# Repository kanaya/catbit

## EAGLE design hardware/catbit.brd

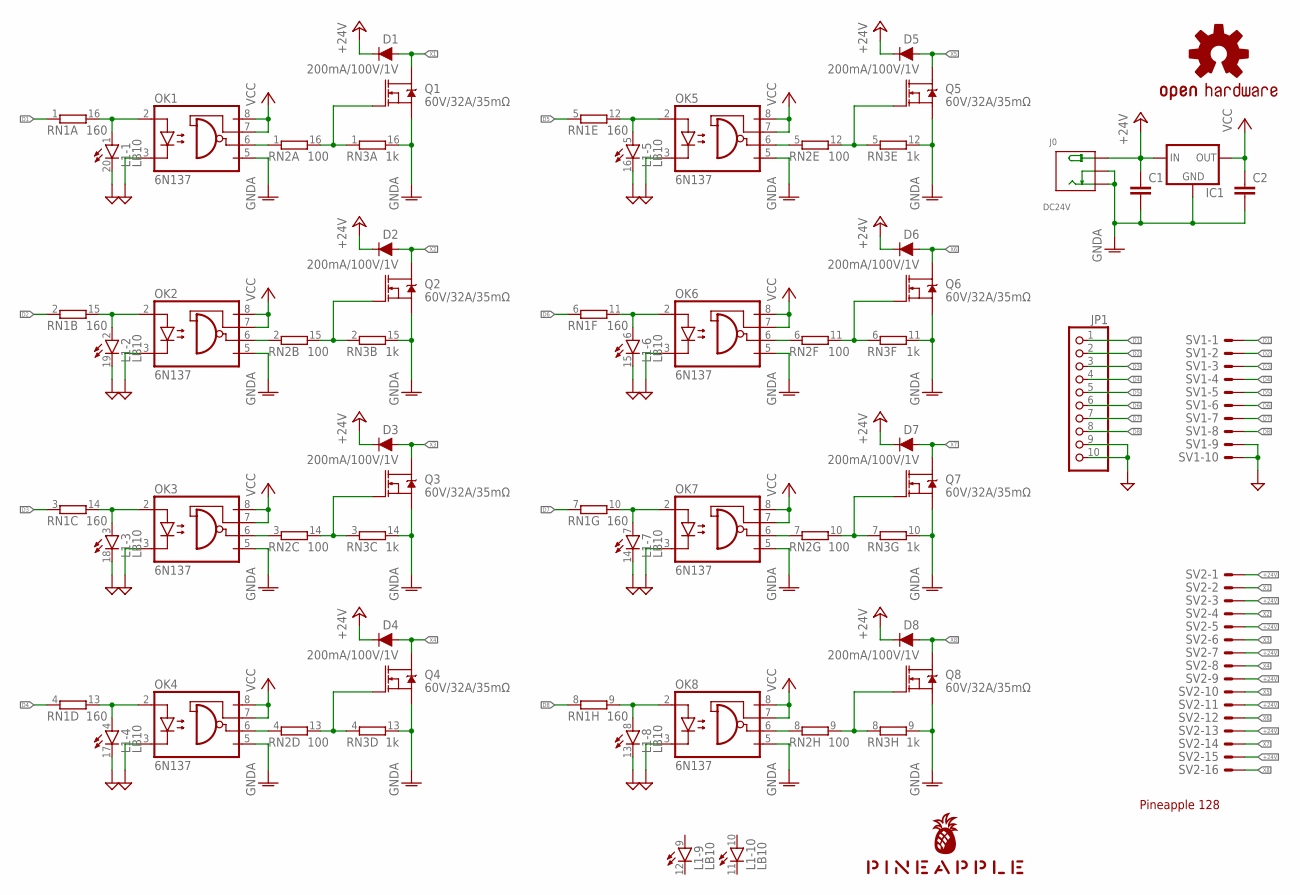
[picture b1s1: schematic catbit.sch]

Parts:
C1, C2: C-EU025-024X044; C025-024X044
D1, D2, D3, D4, D5, D6, D7, D8: 200mA/100V/1V; DIODE-1N4148
IC1: 78XXS
J0: DC24V; 3P-L14.2*W11.0*H9.0MM
JP1: PINHD-1X10; 1X10
L1: LB10
LOGO1: OSHW-LOGOS-COPPER; OSHW-LOGO-S_COPPER
OK1, OK2, OK3, OK4, OK5, OK6, OK7, OK8: 6N137; DIL08
Q1, Q2, Q3, Q4, Q5, Q6, Q7, Q8: 60V/32A/35mΩ; TO220V
RN1: 160; DIL16
RN2: 100; DIL16
RN3: 1k; DIL16
SV1: ML10LE; ML10L
SV2: ML16LE; ML16L
U$1: PINEAPPLE450_SILK

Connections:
+24V: C1.1, D1.C, D2.C, D3.C, D4.C, D5.C, D6.C, D7.C, D8.C, IC1.IN, J0.+, SV2.1, SV2.3, SV2.5, SV2.7, SV2.9, SV2.11, SV2.13, SV2.15
D1: JP1.1, RN1.1, SV1.1
D2: JP1.2, RN1.2 (1), SV1.2
D3: JP1.3, RN1.3 (1), SV1.3
D4: JP1.4, RN1.4 (1), SV1.4
D5: JP1.5, RN1.5 (1), SV1.5
D6: JP1.6, RN1.6 (1), SV1.6
D7: JP1.7, RN1.7 (1), SV1.7
D8: JP1.8, RN1.8 (1), SV1.8
GND: JP1.9, JP1.10, L1.13 (C), L1.14 (C), L1.15 (C), L1.16 (C), L1.17 (C), L1.18 (C), L1.19 (C), L1.20 (C), OK1.3 (C), OK2.3 (C), OK3.3 (C), OK4.3 (C), OK5.3 (C), OK6.3 (C), OK7.3 (C), OK8.3 (C), SV1.9, SV1.10
GNDA: C1.2, C2.2, IC1.GND, J0.-1 (-), J0.-2 (CDN), OK1.5 (GND), OK2.5 (GND), OK3.5 (GND), OK4.5 (GND), OK5.5 (GND), OK6.5 (GND), OK7.5 (GND), OK8.5 (GND), Q1.3 (S), Q2.3 (S), Q3.3 (S), Q4.3 (S), Q5.3 (S), Q6.3 (S), Q7.3 (S), Q8.3 (S), RN3.9 (2), RN3.10 (2), RN3.11 (2), RN3.12 (2), RN3.13 (2), RN3.14 (2), RN3.15 (2), RN3.16 (2)
unnamed: L1.1 (A), OK1.2 (A), RN1.16 (2)
unnamed: OK1.6 (VO), RN2.1
unnamed: Q1.1 (G), RN2.16 (2), RN3.1
unnamed: L1.2 (A), OK2.2 (A), RN1.15 (2)
unnamed: OK2.6 (VO), RN2.2 (1)
unnamed: Q2.1 (G), RN2.15 (2), RN3.2 (1)
unnamed: L1.3 (A), OK3.2 (A), RN1.14 (2)
unnamed: OK3.6 (VO), RN2.3 (1)
unnamed: Q3.1 (G), RN2.14 (2), RN3.3 (1)
unnamed: L1.4 (A), OK4.2 (A), RN1.13 (2)
unnamed: OK4.6 (VO), RN2.4 (1)
unnamed: Q4.1 (G), RN2.13 (2), RN3.4 (1)
unnamed: L1.5 (A), OK5.2 (A), RN1.12 (2)
unnamed: OK5.6 (VO), RN2.5 (1)
unnamed: Q5.1 (G), RN2.12 (2), RN3.5 (1)
unnamed: L1.6 (A), OK6.2 (A), RN1.11 (2)
unnamed: OK6.6 (VO), RN2.6 (1)
unnamed: Q6.1 (G), RN2.11 (2), RN3.6 (1)
unnamed: L1.7 (A), OK7.2 (A), RN1.10 (2)
unnamed: OK7.6 (VO), RN2.7 (1)
unnamed: Q7.1 (G), RN2.10 (2), RN3.7 (1)
unnamed: L1.8 (A), OK8.2 (A), RN1.9 (2)
unnamed: OK8.6 (VO), RN2.8 (1)
unnamed: Q8.1 (G), RN2.9 (2), RN3.8 (1)
VCC: C2.1, IC1.OUT, OK1.7 (VE), OK1.8 (VCC), OK2.7 (VE), OK2.8 (VCC), OK3.7 (VE), OK3.8 (VCC), OK4.7 (VE), OK4.8 (VCC), OK5.7 (VE), OK5.8 (VCC), OK6.7 (VE), OK6.8 (VCC), OK7.7 (VE), OK7.8 (VCC), OK8.7 (VE), OK8.8 (VCC)
X1: D1.A, Q1.2 (D), SV2.2
X2: D2.A, Q2.2 (D), SV2.4
X3: D3.A, Q3.2 (D), SV2.6
X4: D4.A, Q4.2 (D), SV2.8
X5: D5.A, Q5.2 (D), SV2.10
X6: D6.A, Q6.2 (D), SV2.12
X7: D7.A, Q7.2 (D), SV2.14
X8: D8.A, Q8.2 (D), SV2.16

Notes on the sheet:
Pineapple 128

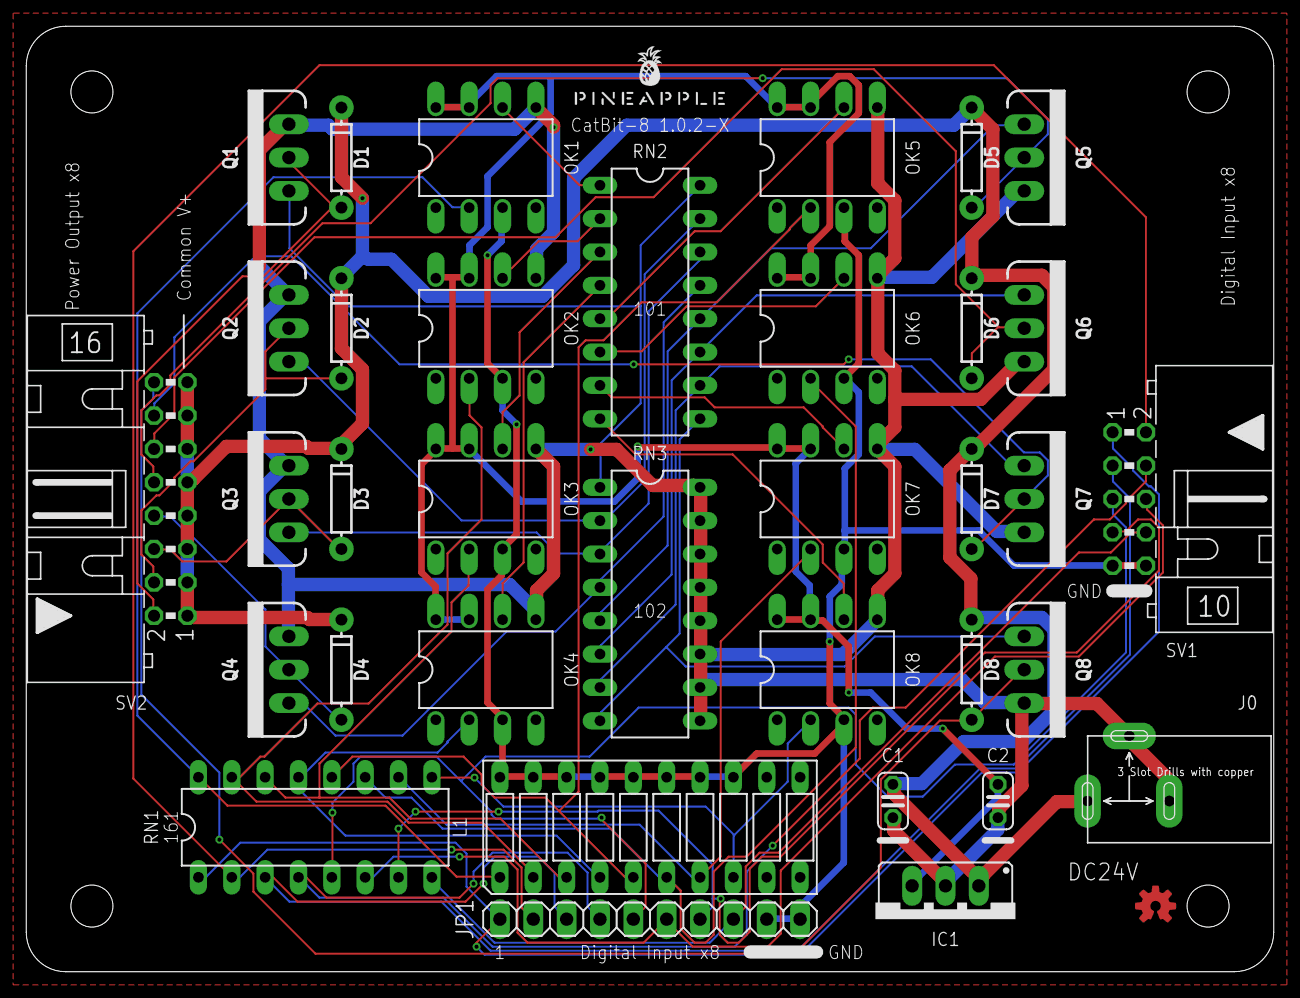
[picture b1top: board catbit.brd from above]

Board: 2 copper layers, 94.9 x 71.9 mm, 37 parts (0 on the bottom side), 44 nets.

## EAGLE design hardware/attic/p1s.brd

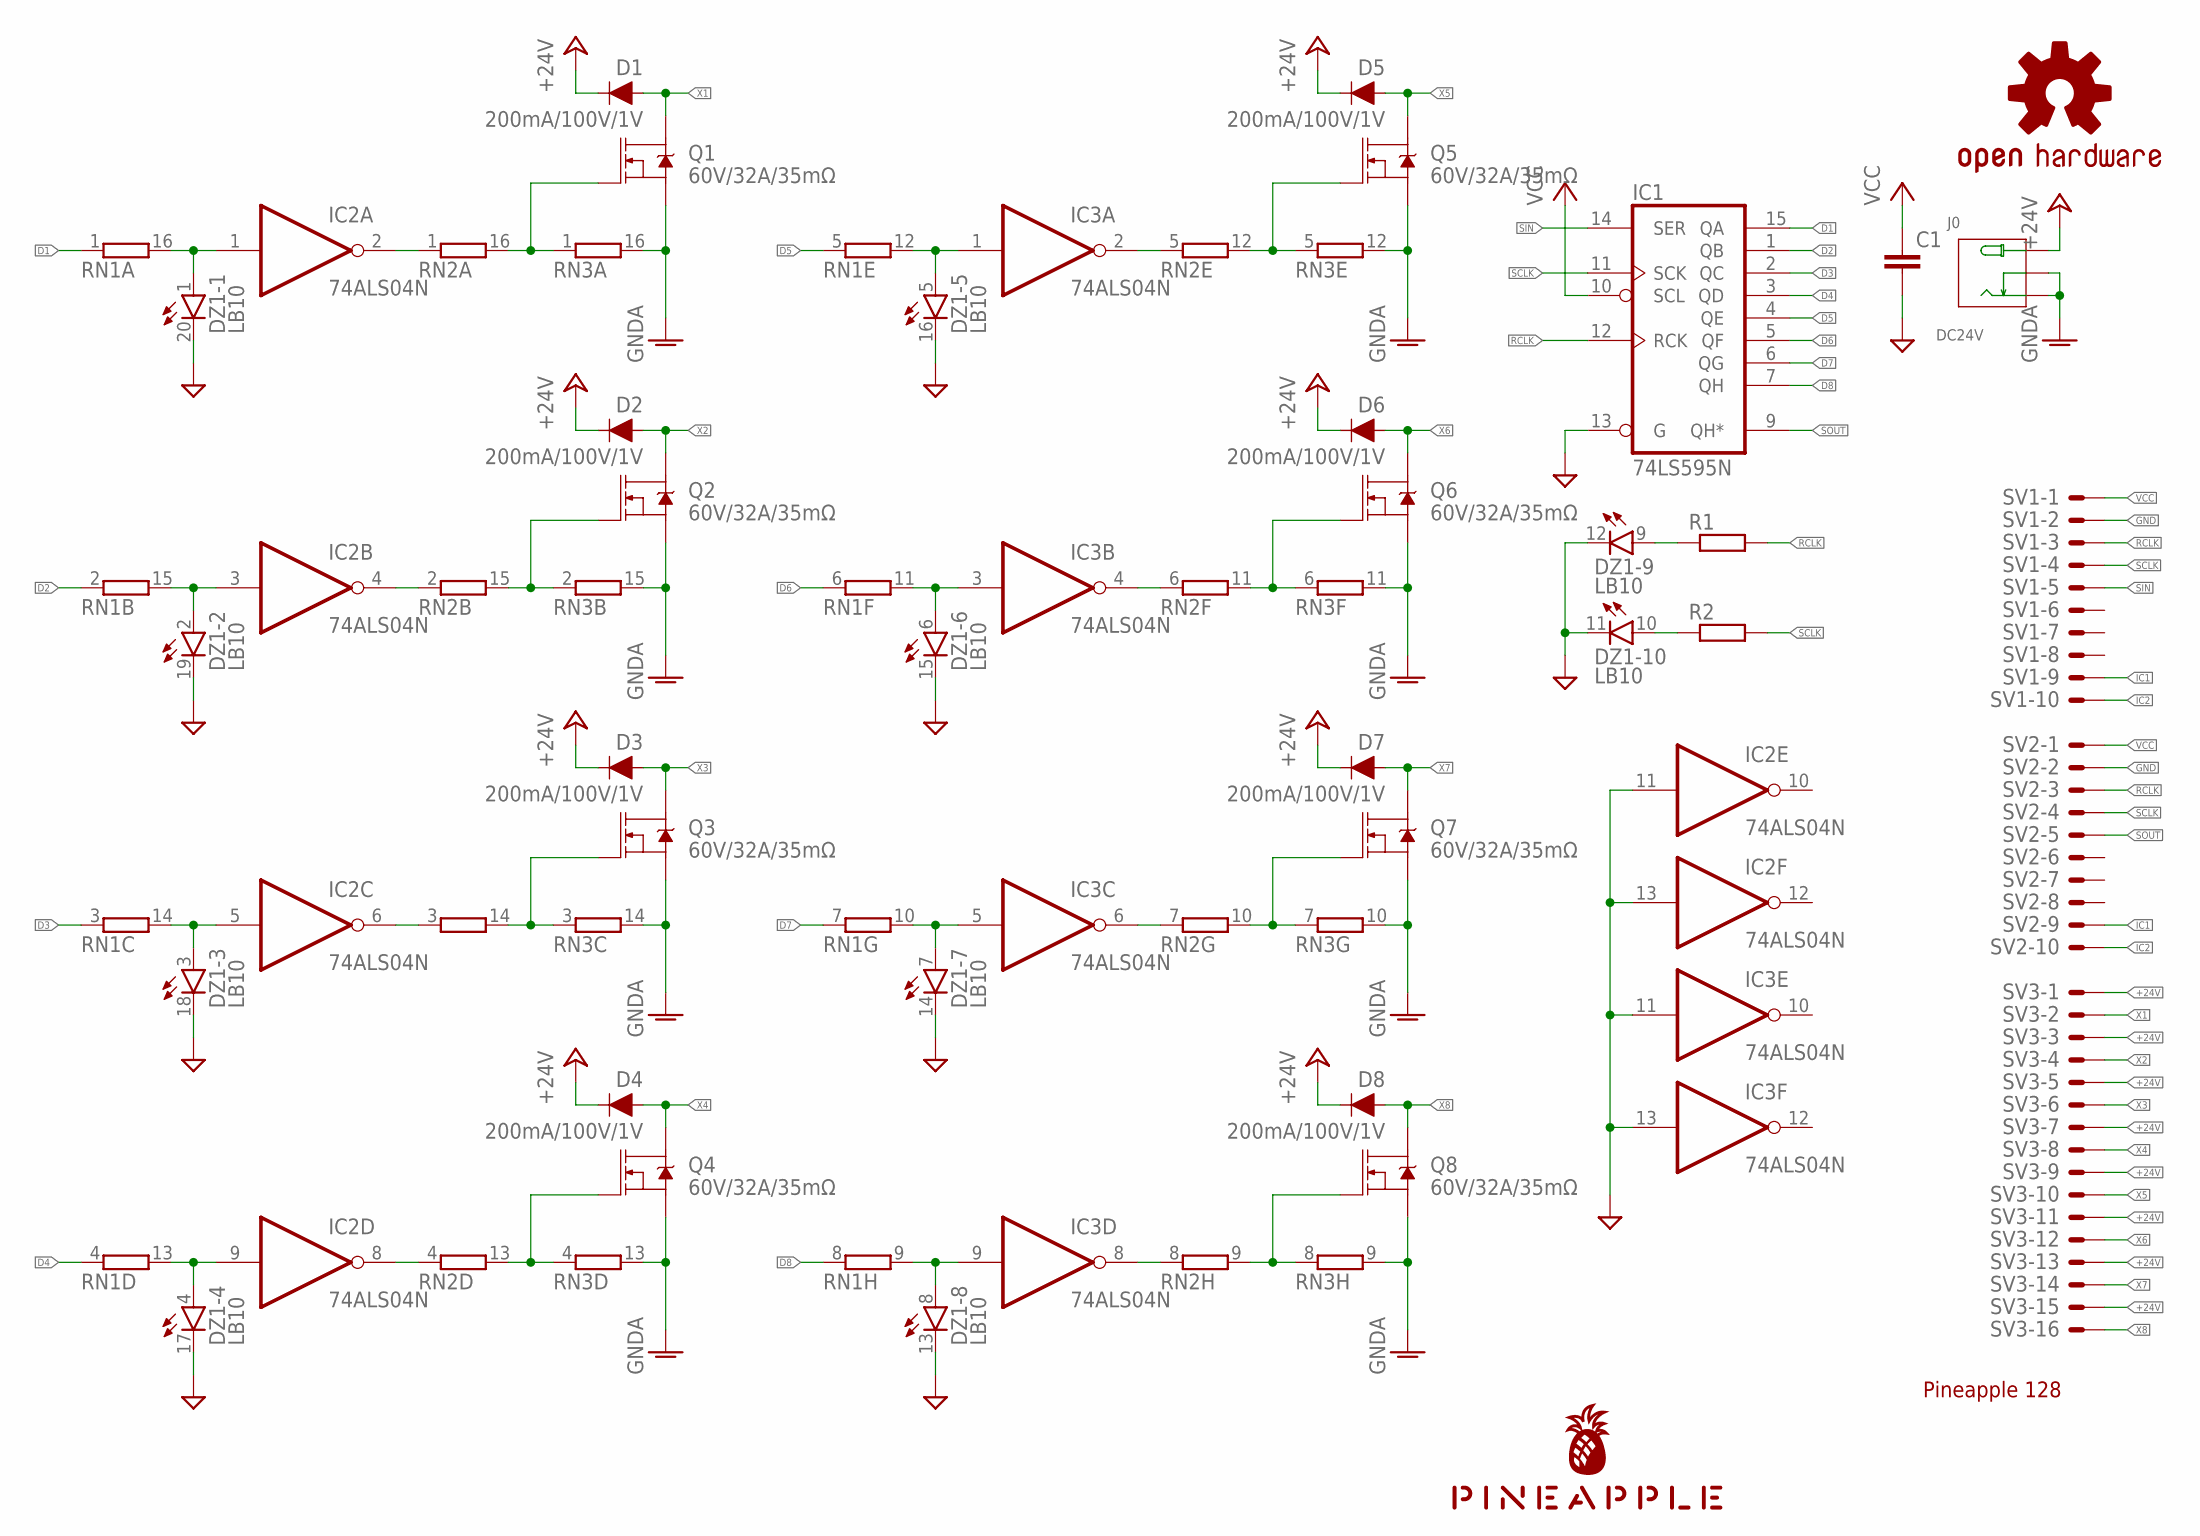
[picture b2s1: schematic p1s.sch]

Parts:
C1: C-EU025-024X044; C025-024X044
D1, D2, D3, D4, D5, D6, D7, D8: 200mA/100V/1V; DIODE-1N4148
DZ1: LB10
IC1: 74LS595N; DIL16
IC2, IC3: 74ALS04N; DIL14
J0: DC24V; 3P-L14.2*W11.0*H9.0MM
LOGO1: OSHW-LOGOS-COPPER; OSHW-LOGO-S_COPPER
Q1, Q2, Q3, Q4, Q5, Q6, Q7, Q8: 60V/32A/35mΩ; TO220V
R1, R2: R-EU_0204/5; 0204/5
RN1, RN2, RN3: 8R-N; DIL16
SV1, SV2: ML10LE; ML10L
SV3: ML16LE; ML16L
U$1: PINEAPPLE450_SILK

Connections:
+24V: D1.C, D2.C, D3.C, D4.C, D5.C, D6.C, D7.C, D8.C, J0.+, SV3.1, SV3.3, SV3.5, SV3.7, SV3.9, SV3.11, SV3.13, SV3.15
D1: IC1.15 (QA), RN1.1
D2: IC1.1 (QB), RN1.2 (1)
D3: IC1.2 (QC), RN1.3 (1)
D4: IC1.3 (QD), RN1.4 (1)
D5: IC1.4 (QE), RN1.5 (1)
D6: IC1.5 (QF), RN1.6 (1)
D7: IC1.6 (QG), RN1.7 (1)
D8: IC1.7 (QH), RN1.8 (1)
GND: C1.2, DZ1.11 (C), DZ1.12 (C), DZ1.13 (C), DZ1.14 (C), DZ1.15 (C), DZ1.16 (C), DZ1.17 (C), DZ1.18 (C), DZ1.19 (C), DZ1.20 (C), IC1.8 (GND), IC1.13 (G), IC2.7 (GND), IC2.11 (I), IC2.13 (I), IC3.7 (GND), IC3.11 (I), IC3.13 (I), SV1.2, SV2.2
GNDA: J0.-1 (-), J0.-2 (CDN), Q1.3 (S), Q2.3 (S), Q3.3 (S), Q4.3 (S), Q5.3 (S), Q6.3 (S), Q7.3 (S), Q8.3 (S), RN3.9 (2), RN3.10 (2), RN3.11 (2), RN3.12 (2), RN3.13 (2), RN3.14 (2), RN3.15 (2), RN3.16 (2)
IC1: SV1.9, SV2.9
IC2: SV1.10, SV2.10
unnamed: DZ1.1 (A), IC2.1 (I), RN1.16 (2)
unnamed: IC2.2 (O), RN2.1
unnamed: Q1.1 (G), RN2.16 (2), RN3.1
unnamed: DZ1.2 (A), IC2.3 (I), RN1.15 (2)
unnamed: IC2.4 (O), RN2.2 (1)
unnamed: Q2.1 (G), RN2.15 (2), RN3.2 (1)
unnamed: DZ1.3 (A), IC2.5 (I), RN1.14 (2)
unnamed: IC2.6 (O), RN2.3 (1)
unnamed: Q3.1 (G), RN2.14 (2), RN3.3 (1)
unnamed: DZ1.4 (A), IC2.9 (I), RN1.13 (2)
unnamed: IC2.8 (O), RN2.4 (1)
unnamed: Q4.1 (G), RN2.13 (2), RN3.4 (1)
unnamed: DZ1.5 (A), IC3.1 (I), RN1.12 (2)
unnamed: IC3.8 (O), RN2.8 (1)
unnamed: Q5.1 (G), RN2.12 (2), RN3.5 (1)
unnamed: DZ1.6 (A), IC3.3 (I), RN1.11 (2)
unnamed: IC3.6 (O), RN2.7 (1)
unnamed: Q6.1 (G), RN2.11 (2), RN3.6 (1)
unnamed: DZ1.7 (A), IC3.5 (I), RN1.10 (2)
unnamed: IC3.4 (O), RN2.6 (1)
unnamed: Q7.1 (G), RN2.10 (2), RN3.7 (1)
unnamed: DZ1.8 (A), IC3.9 (I), RN1.9 (2)
unnamed: IC3.2 (O), RN2.5 (1)
unnamed: Q8.1 (G), RN2.9 (2), RN3.8 (1)
unnamed: DZ1.9 (A), R1.1
unnamed: DZ1.10 (A), R2.1
RCLK: IC1.12 (RCK), R1.2, SV1.3, SV2.3
SCLK: IC1.11 (SCK), R2.2, SV1.4, SV2.4
SIN: IC1.14 (SER), SV1.5
SOUT: IC1.9 (QH*), SV2.5
VCC: C1.1, IC1.10 (SCL), IC1.16 (VCC), IC2.14 (VCC), IC3.14 (VCC), SV1.1, SV2.1
X1: D1.A, Q1.2 (D), SV3.2
X2: D2.A, Q2.2 (D), SV3.4
X3: D3.A, Q3.2 (D), SV3.6
X4: D4.A, Q4.2 (D), SV3.8
X5: D5.A, Q5.2 (D), SV3.10
X6: D6.A, Q6.2 (D), SV3.12
X7: D7.A, Q7.2 (D), SV3.14
X8: D8.A, Q8.2 (D), SV3.16

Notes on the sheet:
Pineapple 128

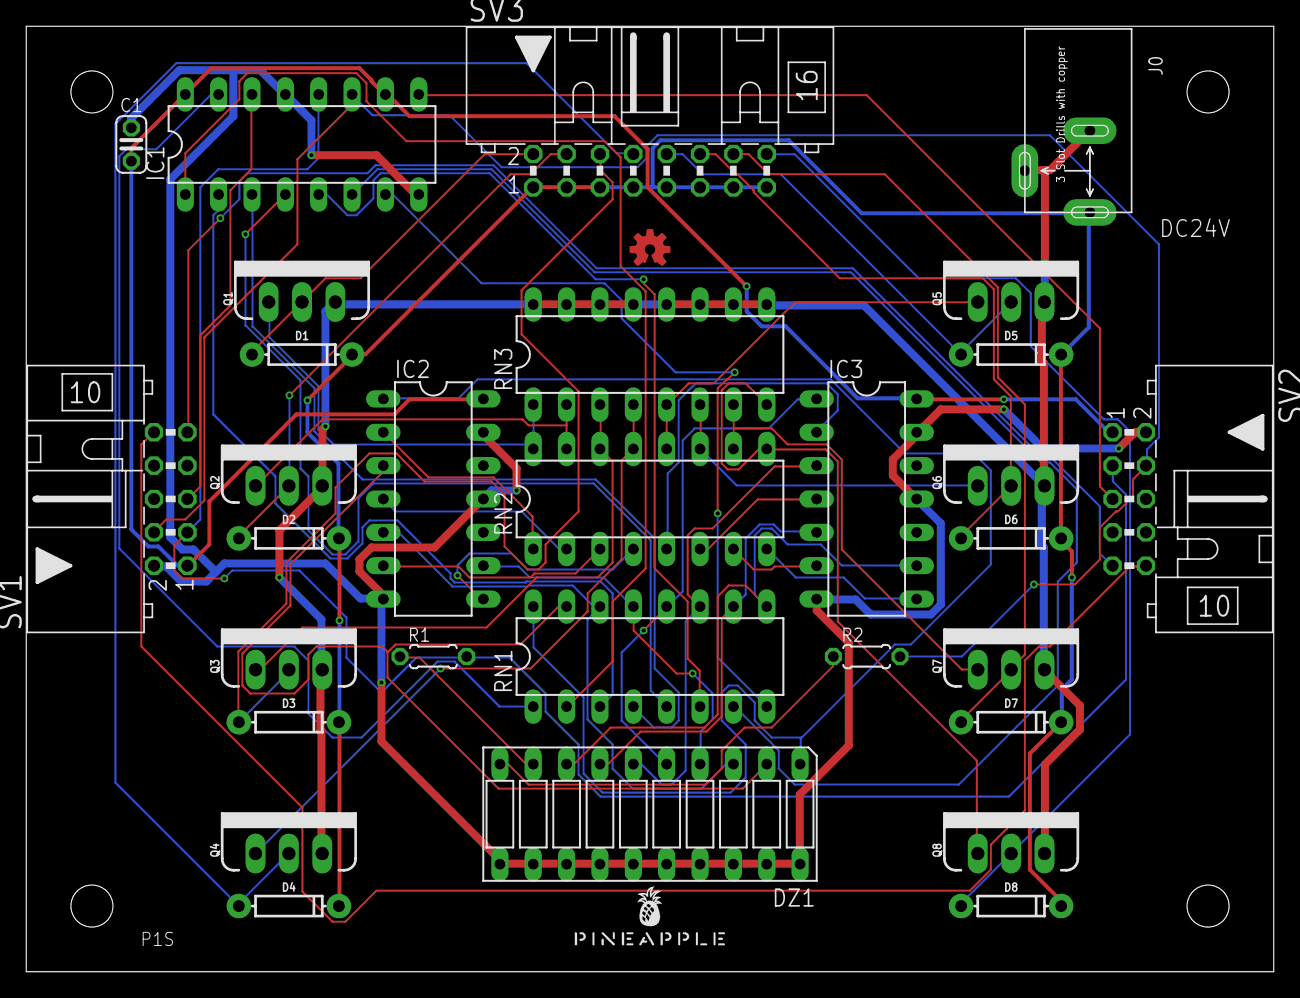
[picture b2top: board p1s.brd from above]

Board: 2 copper layers, 94.9 x 71.9 mm, 32 parts (0 on the bottom side), 52 nets.

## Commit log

2020-06-24 Added .gitignore
2020-06-24 First try.
2020-06-24 Added P1S board.
2020-06-24 Updated P1S.
2020-06-24 Added P1.
2020-06-25 Removed capacitance value.
2020-06-25 Moved prototype of Pineapple I to the attic.
2020-06-25 Design of the board.
2020-06-26 Silk.
2021-09-20 Corner rounding.
2021-09-20 Renamed DZ1 to L1.
2021-10-05 Removed unnecessary silks and added GND marks.
2021-10-10 Better power handling.
2021-10-12 Fixed GND separation.
2021-10-31 Clean up around OUTPUT port.

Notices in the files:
parts and their libraries:
SparkFun-Aesthetics: Licensing: Creative Commons ShareAlike 4.0 International - https://creativecommons.org/licenses/by-sa/4.0
